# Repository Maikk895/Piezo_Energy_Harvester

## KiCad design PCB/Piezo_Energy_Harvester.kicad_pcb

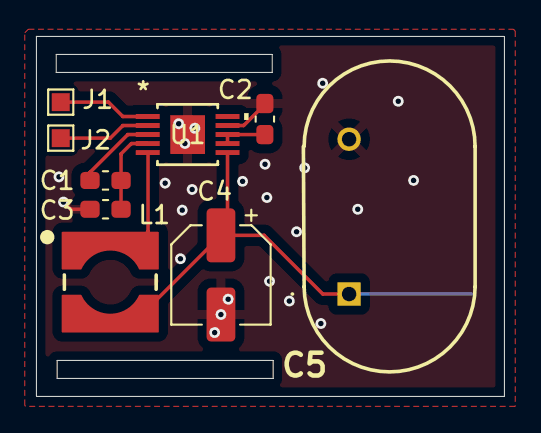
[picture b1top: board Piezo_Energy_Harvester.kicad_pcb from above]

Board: 2 copper layers, 26.0 x 20.0 mm, 9 parts (0 on the bottom side), 8 nets.

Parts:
C1: 1u 6V; C_0603_1608Metric_Pad1.08x0.95mm_HandSolder
C2: 4.7u 6V; C_0603_1608Metric_Pad1.08x0.95mm_HandSolder
C3: 10u 25V; C_0603_1608Metric_Pad1.08x0.95mm_HandSolder
C4: 47u 6V; CP_Elec_5x5.4
C5: Super_Cap; BMOD0001P005B02
J1, J2: Conn_01x01_Pin; TestPoint_Pad_1.0x1.0mm
L1: 10u; WE-HEPC_5030
U1: LTC3588IMSE-1-PBF; MSOP-10_MSE_LIT

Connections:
+3.3V: C4.1, C5.1, L1.2, U1.6 (VOUT)
GND: C2.2, C3.1, C4.2, C5.2, U1.9 (D0), U1.EPAD
unnamed: J1.1, U1.1 (PZ1)
unnamed: J2.1, U1.2 (PZ2)
unnamed: C1.1, U1.3 (CAP)
unnamed: C2.1, U1.7 (VIN2), U1.8 (D1)
unnamed: L1.1, U1.5 (SW)
unnamed: C1.2, C3.2, U1.4 (VIN)

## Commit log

2025-11-23 Git ignore added
2026-01-05 change of footprint
2026-01-05 changed coil footprint
2026-01-08 C4 changed
2026-01-08 Minor fix
2026-01-08 Minor changes
2026-01-08 Gerber files added
